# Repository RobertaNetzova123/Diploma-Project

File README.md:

# Diploma-Project
This repository represents the work progress on the diploma project "Automated Pill Dispenser". Codes for hardware control, Mosquitto communication and Node.js user interface versions will be uploaded.

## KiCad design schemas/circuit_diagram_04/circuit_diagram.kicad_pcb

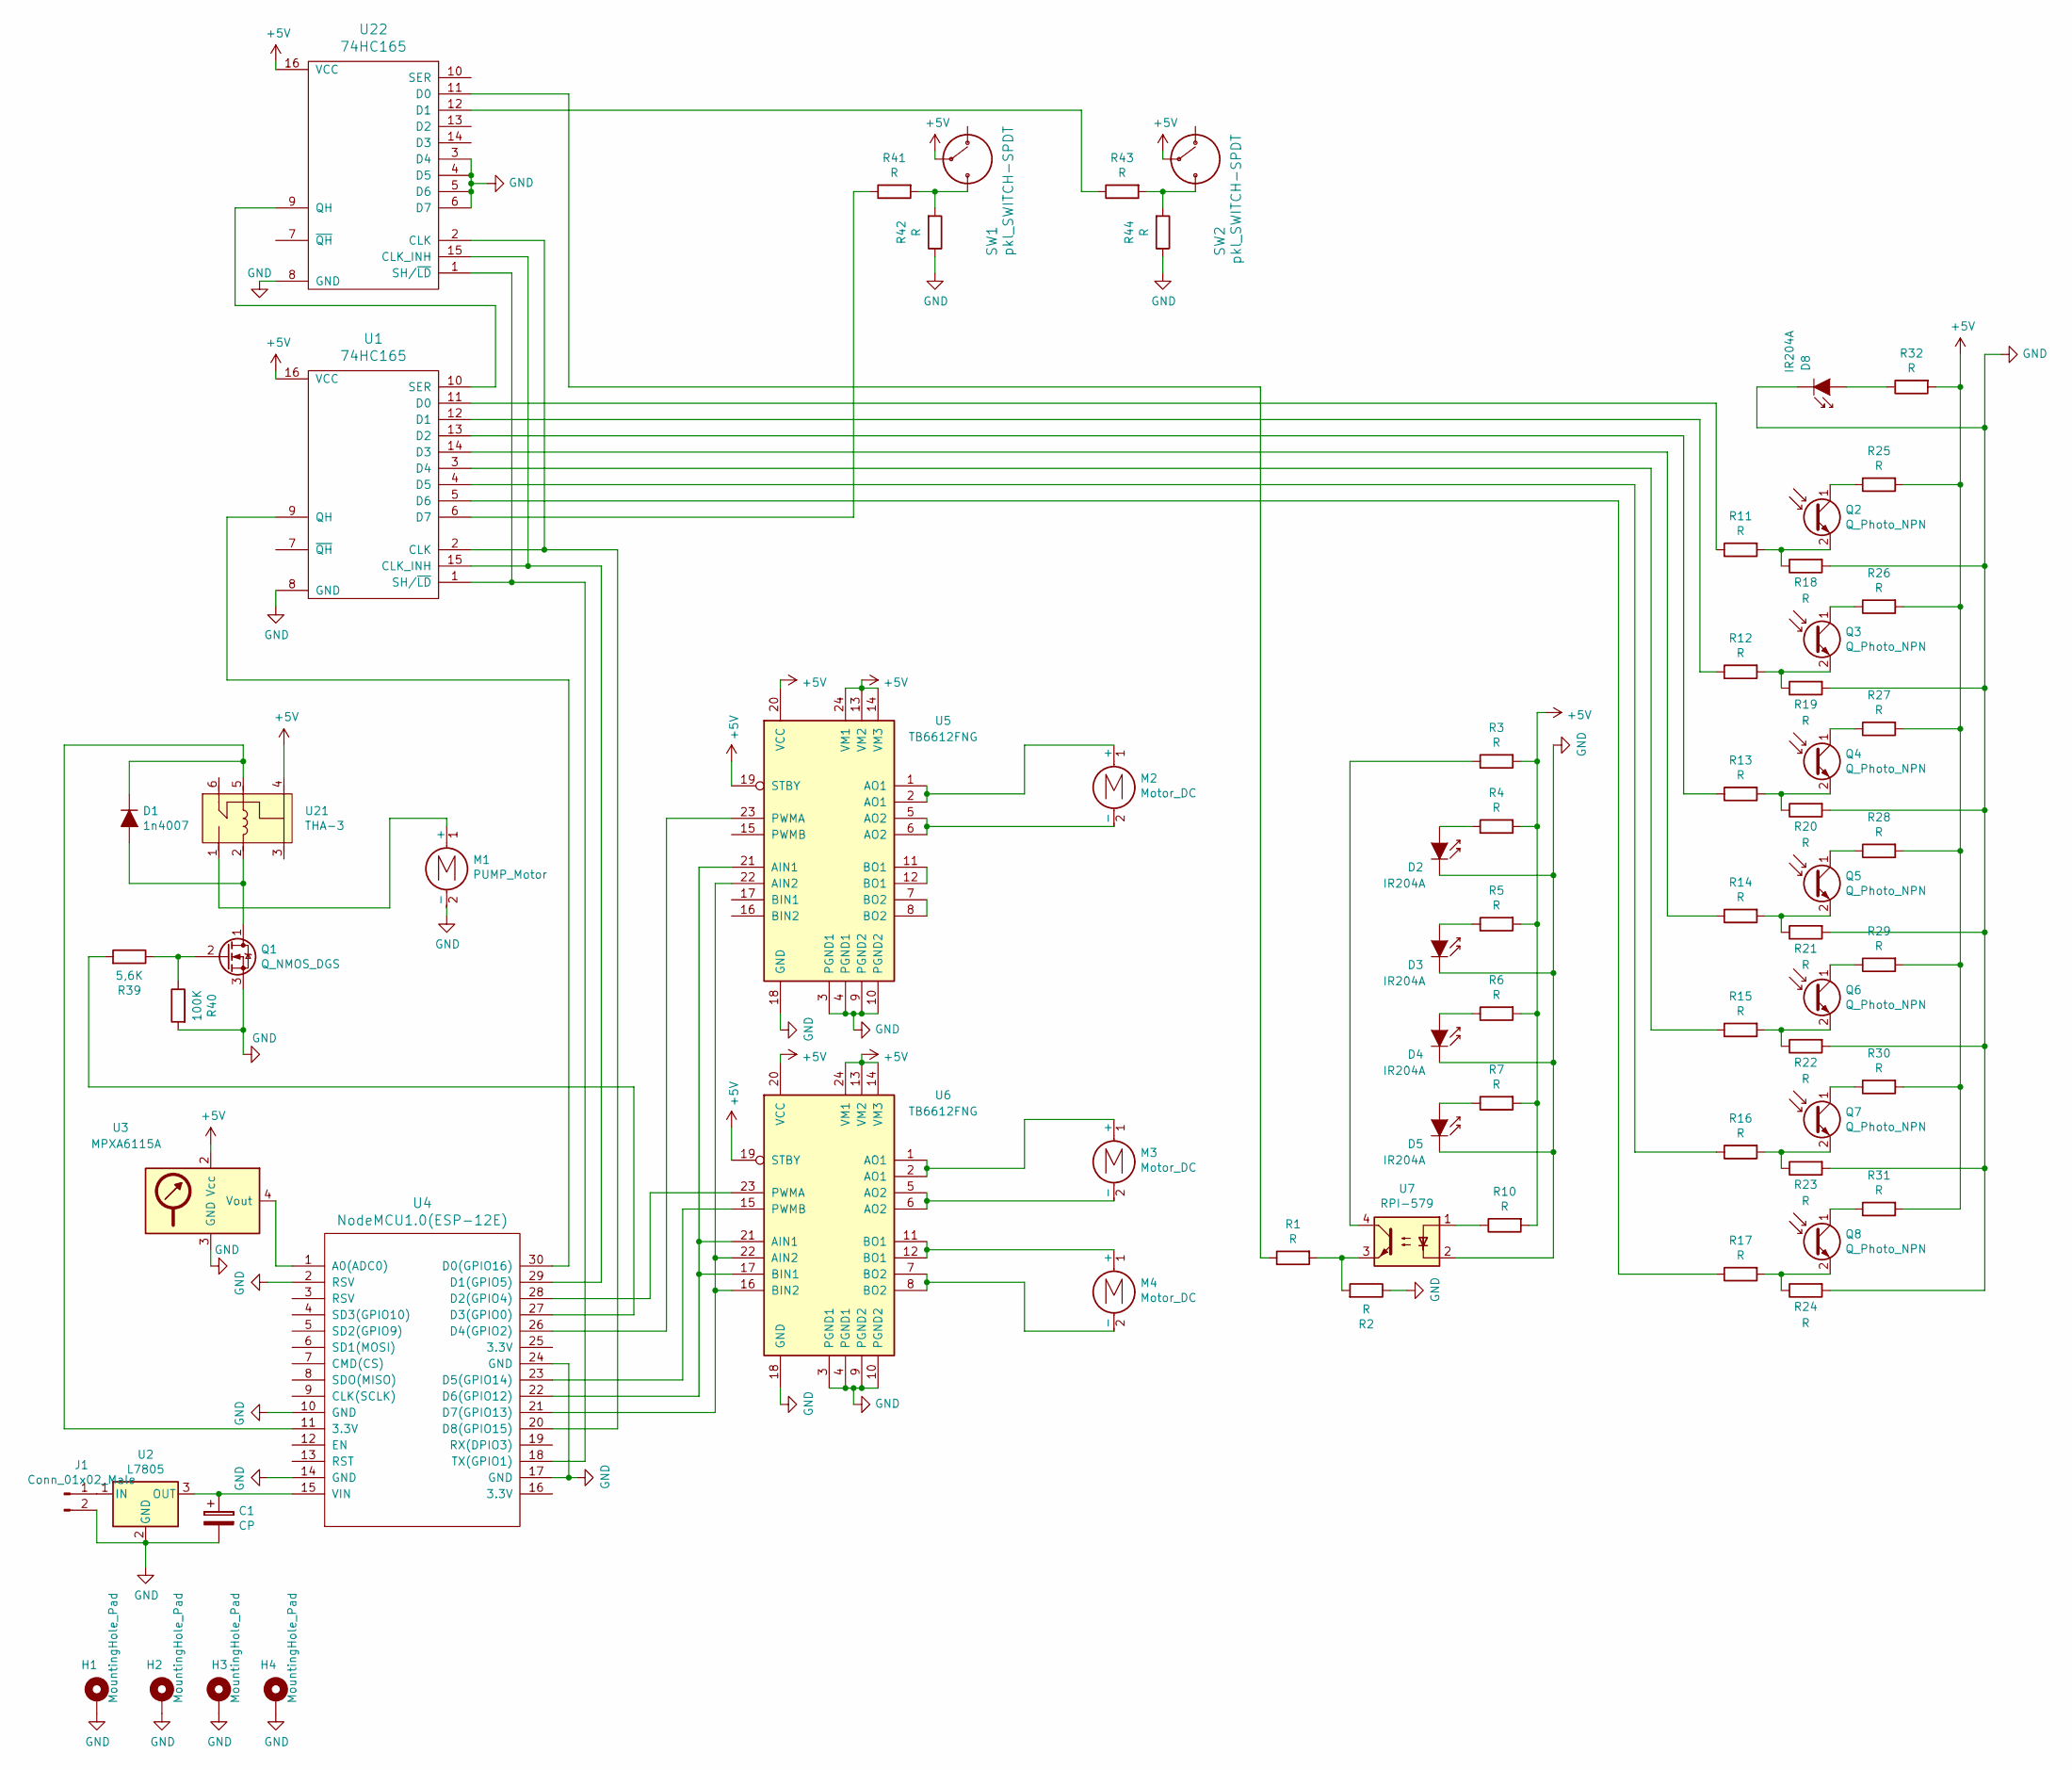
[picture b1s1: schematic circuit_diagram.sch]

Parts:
C1: CP; CP_Radial_D7.5mm_P2.50mm
D1: 1n4007; D_DO-35_SOD27_P7.62mm_Horizontal
D2, D3, D4, D5, D8: IR204A; JWT_A3963_1x02_P3.96mm_Vertical
H1, H2, H3, H4: MountingHole_Pad; MountingHole_4.5mm_Pad
J1: Conn_01x02_Male; TerminalBlock_Altech_AK300-2_P5.00mm
M1: PUMP_Motor; TerminalBlock_Altech_AK300-2_P5.00mm
M2, M3, M4: Motor_DC; TerminalBlock_Altech_AK300-2_P5.00mm
Q1: Q_NMOS_DGS; TO-92L_Inline_Wide
Q2, Q3, Q4, Q5, Q6, Q7, Q8: Q_Photo_NPN; JWT_A3963_1x02_P3.96mm_Vertical
R1, R2, R3, R4, R5, R6, R7, R10, R11, R12, R13, R14, R15, R16, R17, R18, R19, R20, R21, R22, R23, R24, R25, R26, R27, R28, R29, R30, R31, R32, R41, R42, R43, R44: R; R_0805_2012Metric_Pad1.15x1.40mm_HandSolder
R39: 5,6K; R_0805_2012Metric_Pad1.15x1.40mm_HandSolder
R40: 100K; R_0805_2012Metric_Pad1.15x1.40mm_HandSolder
SW1, SW2: pkl_SWITCH-SPDT; PinSocket_1x03_P1.27mm_Vertical
U1, U22: 74HC165; DIP-16_W7.62mm_Socket_LongPads
U2: L7805; TO-220-3_Vertical
U3: MPXA6115A; PinSocket_1x08_P2.54mm_Vertical
U4: NodeMCU1.0(ESP-12E); NodeMCU1.0(12-E)
U5, U6: TB6612FNG; SSOP-24_5.3x8.2mm_P0.65mm
U7: RPI-579; DIP-4_W7.62mm
U21: THA-3; Relay_SPDT_HsinDa_Y14

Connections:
+5V: R3.2, R4.2, R5.2, R6.2, R7.2, R10.2, R25.2, R26.2, R27.2, R28.2, R29.2, R30.2, R31.2, R32.2, SW1.2, SW2.2, U1.16 (VCC), U3.2 (Vcc), U5.13 (VM2), U5.14 (VM3), U5.19 (STBY), U5.20 (VCC), U5.24 (VM1), U6.13 (VM2), U6.14 (VM3), U6.19 (STBY), U6.20 (VCC), U6.24 (VM1), U21.4, U22.16 (VCC)
GND: C1.2, D2.1 (K), D3.1 (K), D4.1 (K), D5.1 (K), D8.1 (K), H1.1, H2.1, H3.1, H4.1, J1.2, M1.2 (-), Q1.3 (S), R2.1, R18.2, R19.2, R20.2, R21.2, R22.2, R23.2, R24.2, R40.2, R42.1, R44.1, U1.8 (GND), U2.2 (GND), U3.3 (GND), U4.2 (RSV), U4.10 (GND), U4.14 (GND), U4.17 (GND), U4.24 (GND), U5.3 (PGND1), U5.4 (PGND1), U5.9 (PGND2), U5.10 (PGND2), U5.18 (GND), U6.3 (PGND1), U6.4 (PGND1), U6.9 (PGND2), U6.10 (PGND2), U6.18 (GND), U7.2, U22.3 (D4), U22.4 (D5), U22.5 (D6), U22.6 (D7), U22.8 (GND)
unnamed: C1.1, U2.3 (OUT), U4.15 (VIN)
unnamed: D1.1 (K), U4.11 (3.3V), U21.5
unnamed: D1.2 (A), Q1.1 (D), U21.2
unnamed: D2.2 (A), R4.1
unnamed: D3.2 (A), R5.1
unnamed: D4.2 (A), R6.1
unnamed: D5.2 (A), R7.1
unnamed: D8.2 (A), R32.1
unnamed: J1.1, U2.1 (IN)
unnamed: M1.1 (+), U21.1
unnamed: M2.1 (+), U5.1 (AO1), U5.2 (AO1)
unnamed: M2.2 (-), U5.5 (AO2), U5.6 (AO2)
unnamed: M3.1 (+), U6.1 (AO1), U6.2 (AO1)
unnamed: M3.2 (-), U6.5 (AO2), U6.6 (AO2)
unnamed: M4.1 (+), U6.11 (BO1), U6.12 (BO1)
unnamed: M4.2 (-), U6.7 (BO2), U6.8 (BO2)
unnamed: Q1.2 (G), R39.1, R40.1
unnamed: Q2.1 (C), R25.1
unnamed: Q2.2 (E), R11.2, R18.1
unnamed: Q3.1 (C), R26.1
unnamed: Q3.2 (E), R12.2, R19.1
unnamed: Q4.1 (C), R27.1
unnamed: Q4.2 (E), R13.2, R20.1
unnamed: Q5.1 (C), R28.1
unnamed: Q5.2 (E), R14.2, R21.1
unnamed: Q6.1 (C), R29.1
unnamed: Q6.2 (E), R15.2, R22.1
unnamed: Q7.1 (C), R30.1
unnamed: Q7.2 (E), R16.2, R23.1
unnamed: Q8.1 (C), R31.1
unnamed: Q8.2 (E), R17.2, R24.1
unnamed: R1.1, U22.11 (D0)
unnamed: R1.2, R2.2, U7.3
unnamed: R3.1, U7.4
unnamed: R10.1, U7.1
unnamed: R11.1, U1.11 (D0)
unnamed: R12.1, U1.12 (D1)
unnamed: R13.1, U1.13 (D2)
unnamed: R14.1, U1.14 (D3)
unnamed: R15.1, U1.3 (D4)
unnamed: R16.1, U1.4 (D5)
unnamed: R17.1, U1.5 (D6)
unnamed: R39.2, U4.27 (D3(GPIO0))
unnamed: R41.1, U1.6 (D7)
unnamed: R41.2, R42.2, SW1.3
unnamed: R43.1, U22.12 (D1)
unnamed: R43.2, R44.2, SW2.3
unnamed: U1.1 (SH/~LD), U4.18 (TX(GPIO1)), U22.1 (SH/~LD)
unnamed: U1.2 (CLK), U4.20 (D8(GPIO15)), U22.2 (CLK)
unnamed: U1.9 (QH), U4.30 (D0(GPIO16))
unnamed: U1.10 (SER), U22.9 (QH)
unnamed: U1.15 (CLK_INH), U4.29 (D1(GPIO5)), U22.15 (CLK_INH)
unnamed: U3.4 (Vout), U4.1 (A0(ADC0))
unnamed: U4.21 (D7(GPIO13)), U5.22 (AIN2), U6.16 (BIN2), U6.22 (AIN2)
unnamed: U4.22 (D6(GPIO12)), U5.21 (AIN1), U6.17 (BIN1), U6.21 (AIN1)
unnamed: U4.23 (D5(GPIO14)), U6.15 (PWMB)
unnamed: U4.26 (D4(GPIO2)), U5.23 (PWMA)
unnamed: U4.28 (D2(GPIO4)), U6.23 (PWMA)
unnamed: U5.7 (BO2), U5.8 (BO2)
unnamed: U5.11 (BO1), U5.12 (BO1)

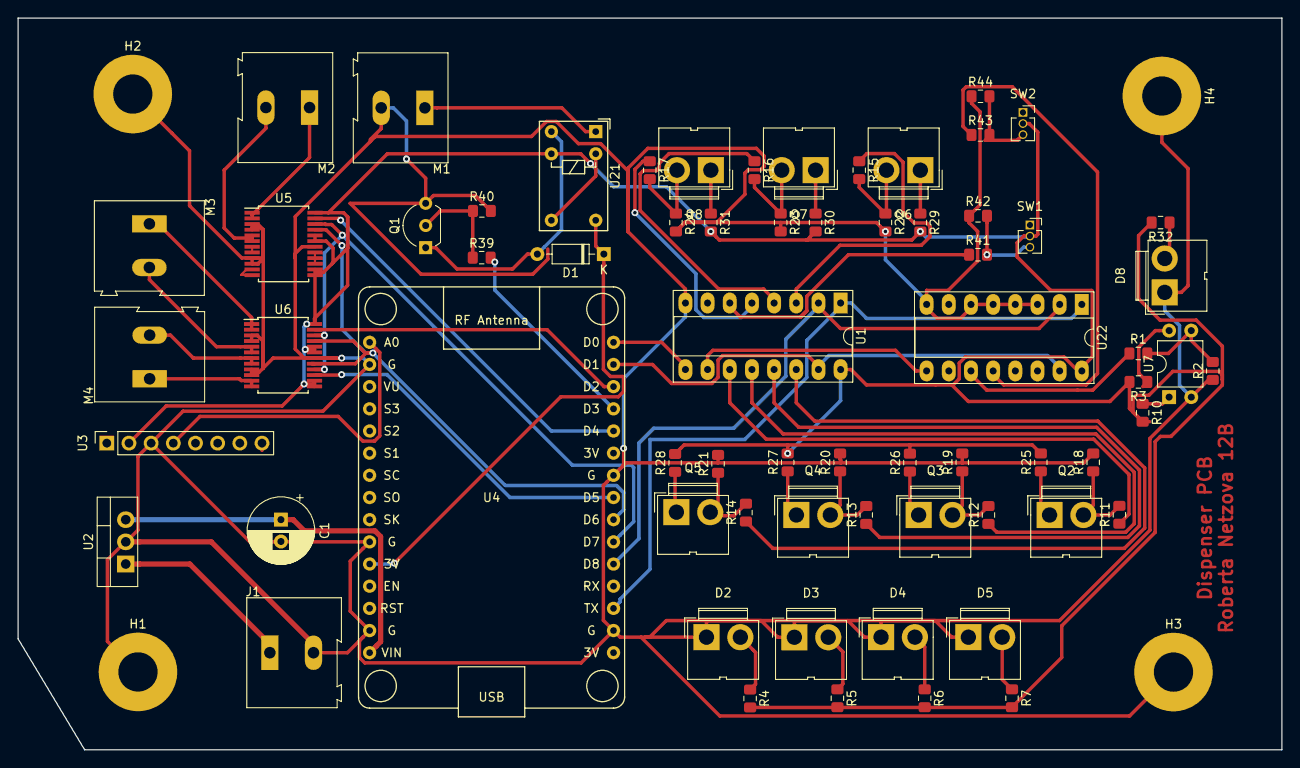
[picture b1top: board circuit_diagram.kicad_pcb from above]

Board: 2 copper layers, 144.8 x 83.8 mm, 71 parts (0 on the bottom side), 62 nets.

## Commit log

2018-12-27 WiFiManager working. Old Mqtt connection
2019-02-05 Ardoino example codes added
2019-02-06 interrupts debouncing logic added
2019-02-12 motor driver code v_02
2019-02-20 Added shift register code 165
2019-02-27 Webb app and circuit diagram commited
2019-03-26 schema, and arduino side v_01.1
2019-04-08 dispenser side; dispenser side with internet
2019-05-16 schemas and Arduino code
2019-05-16 PCB label added
2019-05-26 Web communication fixed
2019-05-28 Pick pill method fixed, drop pill method done, TODO: internet connection
2019-05-29 internet connection created, whole structure connected
2019-05-30 Delay problem fixed
2019-06-01 Handling empty container fixed
2019-06-02 is_pill_picked() function added
2019-06-02 mqtt sending optimized - all containers in one message
2019-06-02 mqtt messaging optimized - one msg for all containers
2019-06-03 MQTT setup function made private
2019-06-05 time exceeded validation when probe is moving down added
2019-06-06 last touches
2019-10-31 Bump lodash from 4.17.11 to 4.17.15 in /Web/dispenserInterface
    Bumps [lodash](https://github.com/lodash/lodash) from 4.17.11 to 4.17.15.
    - [Release notes](https://github.com/lodash/lodash/releases)
    - [Commits](https://github.com/lodash/lodash/compare/4.17.11...4.17.15)
2020-04-30 Bump jquery from 3.3.1 to 3.5.0 in /Web/dispenserInterface
    Bumps [jquery](https://github.com/jquery/jquery) from 3.3.1 to 3.5.0.
    - [Release notes](https://github.com/jquery/jquery/releases)
    - [Commits](https://github.com/jquery/jquery/compare/3.3.1...3.5.0)
2020-07-17 Bump lodash from 4.17.11 to 4.17.19 in /Web/dispenserInterface
    Bumps [lodash](https://github.com/lodash/lodash) from 4.17.11 to 4.17.19.
    - [Release notes](https://github.com/lodash/lodash/releases)
    - [Commits](https://github.com/lodash/lodash/compare/4.17.11...4.17.19)
2021-05-08 Bump lodash from 4.17.11 to 4.17.21 in /Web/dispenserInterface
    Bumps [lodash](https://github.com/lodash/lodash) from 4.17.11 to 4.17.21.
    - [Release notes](https://github.com/lodash/lodash/releases)
    - [Commits](https://github.com/lodash/lodash/compare/4.17.11...4.17.21)
2022-12-08 Bump qs and express in /Web/dispenserInterface
    Bumps [qs](https://github.com/ljharb/qs) to 6.11.0 and updates ancestor dependency [express](https://github.com/expressjs/express). These dependencies need to be updated together.
    Updates `qs` from 6.5.2 to 6.11.0
    - [Release notes](https://github.com/ljharb/qs/releases)
    - [Changelog](https://github.com/ljharb/qs/blob/main/CHANGELOG.md)
    - [Commits](https://github.com/ljharb/qs/compare/v6.5.2...v6.11.0)
    Updates `express` from 4.16.4 to 4.18.2
2022-12-09 Bump express from 4.16.4 to 4.17.3 in /Web/dispenserInterface
    Bumps [express](https://github.com/expressjs/express) from 4.16.4 to 4.17.3.
    - [Release notes](https://github.com/expressjs/express/releases)
    - [Changelog](https://github.com/expressjs/express/blob/master/History.md)
    - [Commits](https://github.com/expressjs/express/compare/4.16.4...4.17.3)
    ---
    updated-dependencies:
